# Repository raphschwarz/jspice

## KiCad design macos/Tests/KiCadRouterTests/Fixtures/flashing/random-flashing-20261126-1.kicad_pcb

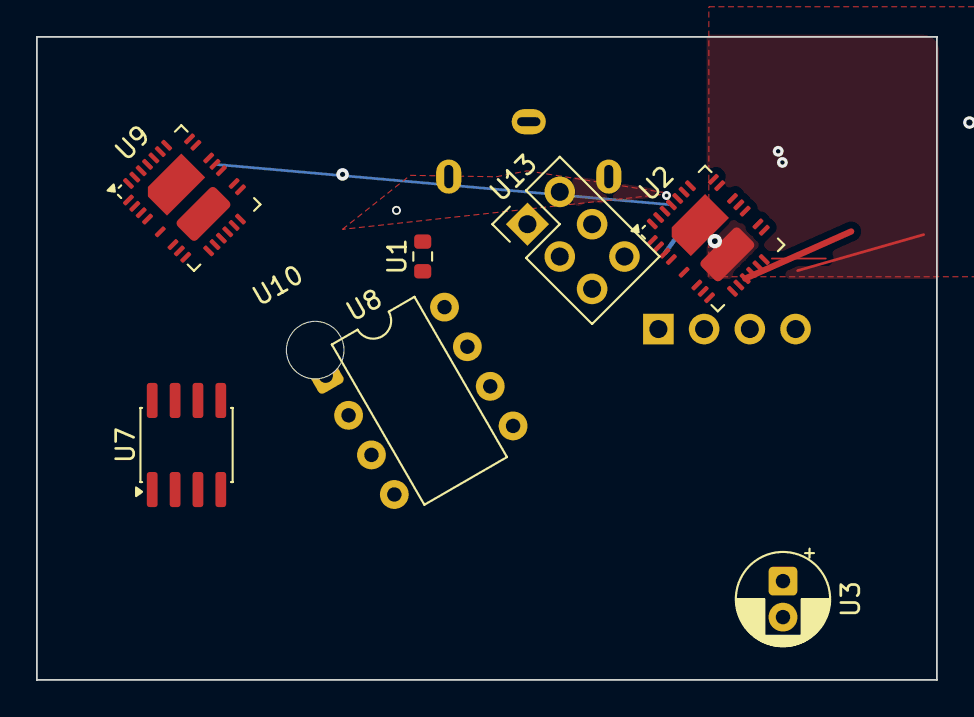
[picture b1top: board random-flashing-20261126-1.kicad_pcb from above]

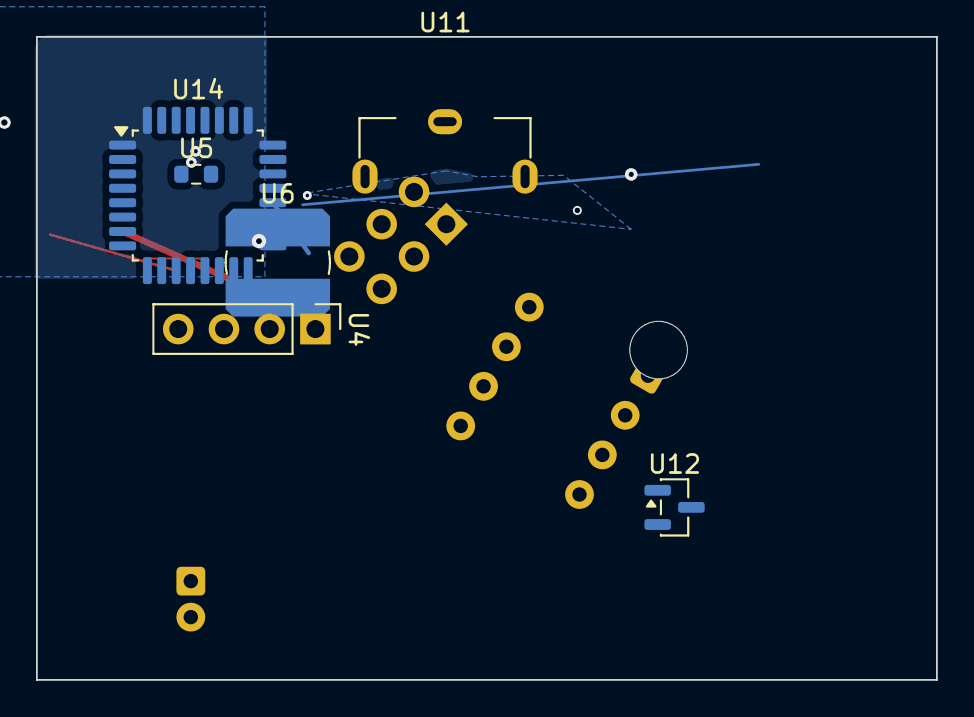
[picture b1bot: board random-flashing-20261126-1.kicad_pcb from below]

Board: 2 copper layers, 50.0 x 35.7 mm, 14 parts (6 on the bottom side), 4 nets.

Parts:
U1, U5: R_0603_1608Metric
U2, U9: Analog_QFN-28-36-2EP_5x6mm_P0.5mm
U3: CP_Radial_D5.0mm_P2.00mm
U4: PinHeader_1x04_P2.54mm_Vertical
U6: L_Bourns_SDR0604
U7: SOIC-8_3.9x4.9mm_P1.27mm
U8: DIP-8_W7.62mm
U10: MountingHole_3.2mm_M3
U11: BatteryHolder_Keystone_590
U12: SOT-23
U13: PinHeader_2x03_P2.54mm_Vertical
U14: LQFP-32_7x7mm_P0.8mm

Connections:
D12: U1.1, U2.1, U2.9, U2.10, U2.14, U2.30, U2.34, U6.2, U7.1, U7.5, U7.7, U8.8, U9.1, U9.31, U11.1, U13.2, U14.3, U14.6, U14.10, U14.12, U14.18, U14.28, U14.29
N1: U2.2, U2.3, U2.17, U2.20, U2.23, U2.31, U2.33, U2.35, U2.37, U4.4, U5.1, U7.2, U8.3, U8.5, U8.7, U9.4, U9.12, U9.15, U9.23, U9.30, U9.34, U9.35, U11.1, U12.1, U13.1, U14.2, U14.5, U14.16
N2: U1.2, U2.6, U2.12, U2.13, U2.38, U3.2, U4.3, U7.6, U8.1, U9.3, U9.6, U9.9, U9.25, U9.38, U14.1, U14.11, U14.19, U14.22, U14.24, U14.25, U14.27, U14.32
VCC: U2.8, U2.15, U2.16, U2.24, U2.36, U3.1, U4.1, U6.1, U8.2, U8.4, U8.6, U9.8, U9.16, U9.21, U9.28, U9.33, U9.36, U12.3, U13.4, U13.6, U14.4, U14.7, U14.13, U14.26, U14.30

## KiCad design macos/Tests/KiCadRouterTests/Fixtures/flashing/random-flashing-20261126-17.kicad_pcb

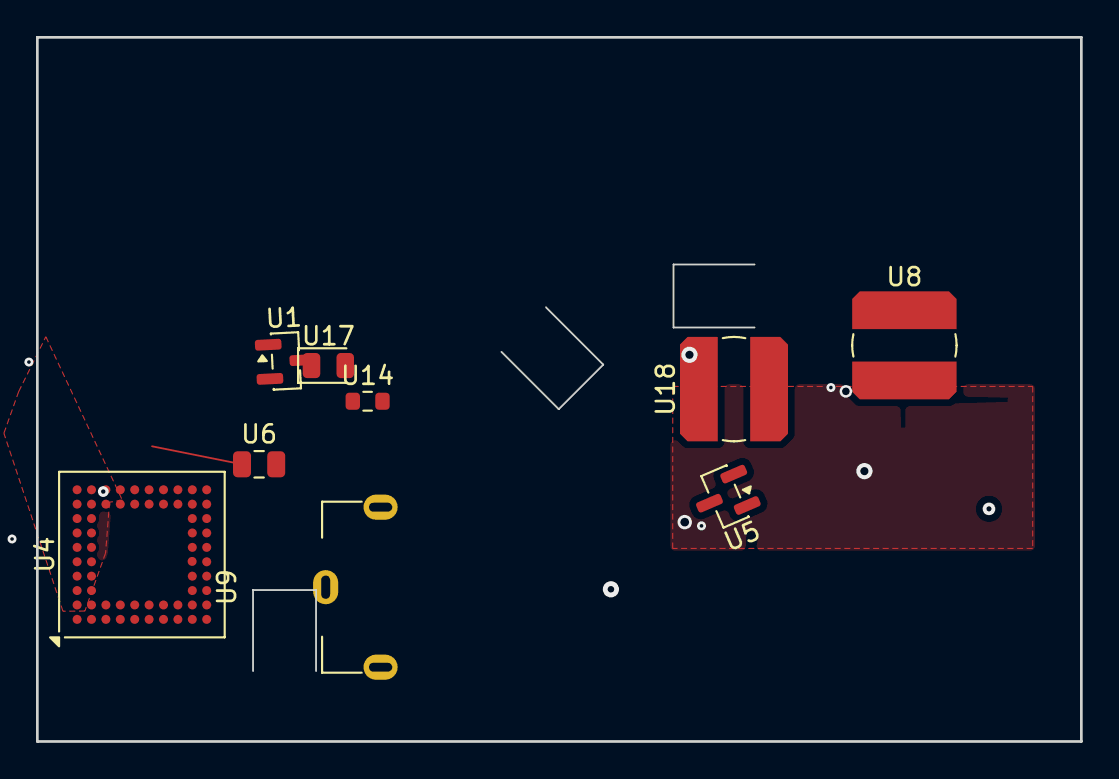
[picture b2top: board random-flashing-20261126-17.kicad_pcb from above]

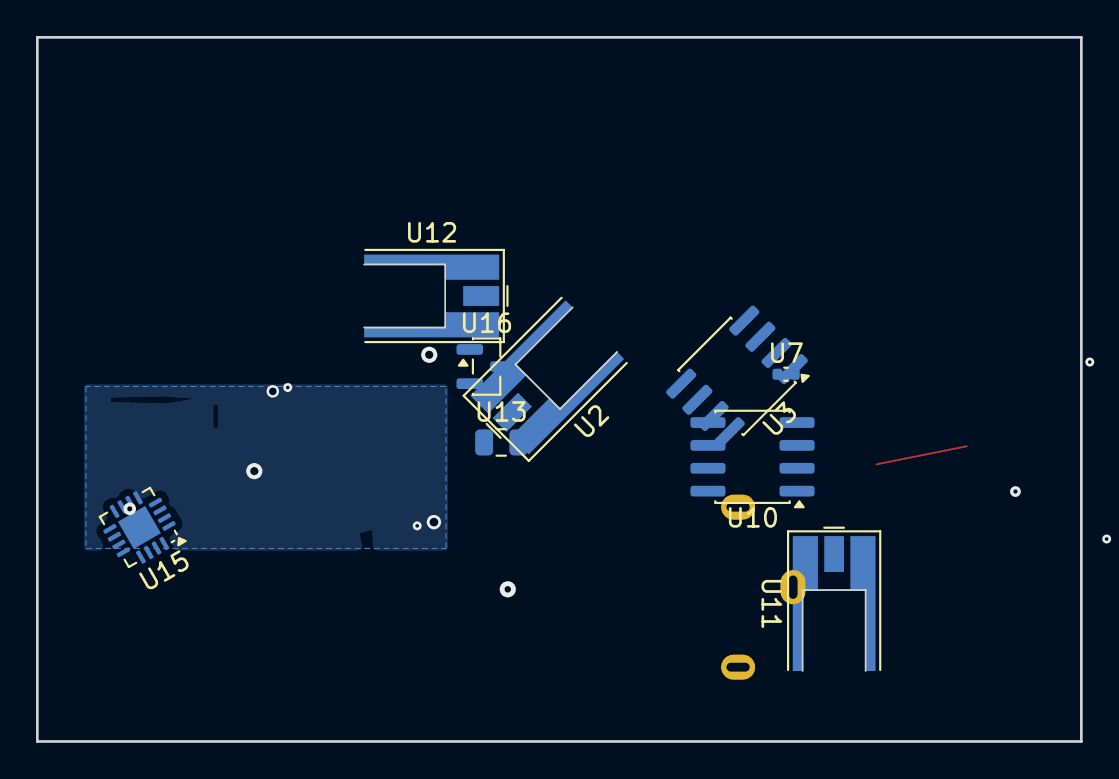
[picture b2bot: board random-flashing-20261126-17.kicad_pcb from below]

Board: 4 copper layers, 58.0 x 39.1 mm, 18 parts (9 on the bottom side), 8 nets.

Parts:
U1, U5, U16: SOT-23
U2, U11, U12: MMCX_Molex_73415-0961_Horizontal_0.8mm-PCB
U3, U10: SOIC-8_3.9x4.9mm_P1.27mm
U4: BGA-64_9.0x9.0mm_Layout10x10_P0.8mm
U6, U13: C_0805_2012Metric
U7: C_0402_1005Metric
U8, U18: L_Bourns_SDR0604
U9: BatteryHolder_Keystone_590
U14: R_0603_1608Metric
U15: QFN-16-1EP_3x3mm_P0.5mm_EP1.75x1.75mm
U17: LED_0805_2012Metric

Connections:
/sub/clk: U1.1, U5.3, U10.5, U10.7, U15.2, U15.12, U15.14
D7: U1.2, U4.B2, U4.B7, U4.G10, U4.H9, U4.J2, U4.J3, U4.K6, U10.1, U10.4, U11.2, U18.1, U18.2
GND: U2.2, U3.8, U4.A10, U4.B8, U4.C10, U4.F9, U4.G2, U4.G9, U4.K2, U8.2, U12.2, U15.5, U15.8, U15.15
N1: U3.2, U4.A7, U4.D1, U4.D9, U4.D10, U4.E1, U4.F2, U4.H10, U4.J4, U4.K8, U10.2, U10.6, U11.1, U13.2, U14.2, U15.7, U15.11, U15.17
N2: U1.3, U3.4, U3.7, U11.2, U15.1
N3: U2.1, U4.B5, U4.F1, U4.H1, U4.J5, U4.K1, U4.K10, U5.1, U6.2, U9.1, U10.3, U12.1, U16.1
PWR1: U3.5, U4.A3, U4.A4, U4.A6, U4.C9, U4.D2, U4.E2, U4.J1, U4.J6, U4.J8, U4.J9, U4.K5, U9.1, U15.3
VCC: U2.2, U4.B3, U4.B4, U4.B10, U4.C2, U4.E9, U4.H2, U4.K9, U14.1, U15.13, U16.2, U17.2

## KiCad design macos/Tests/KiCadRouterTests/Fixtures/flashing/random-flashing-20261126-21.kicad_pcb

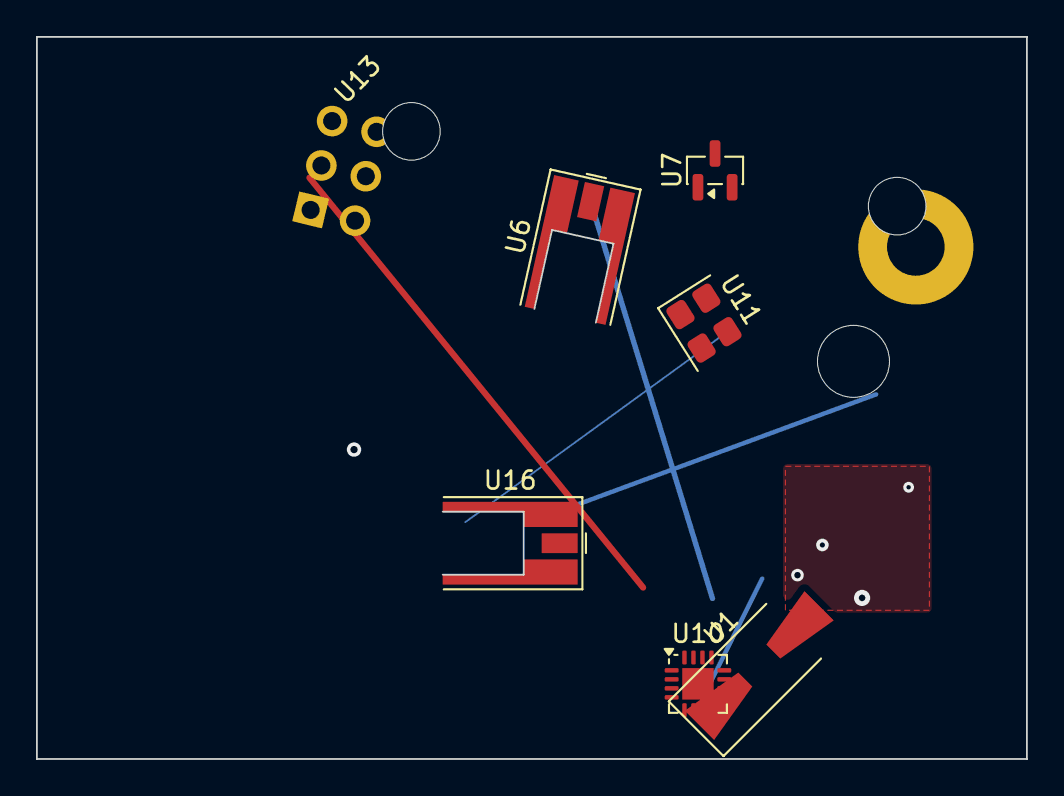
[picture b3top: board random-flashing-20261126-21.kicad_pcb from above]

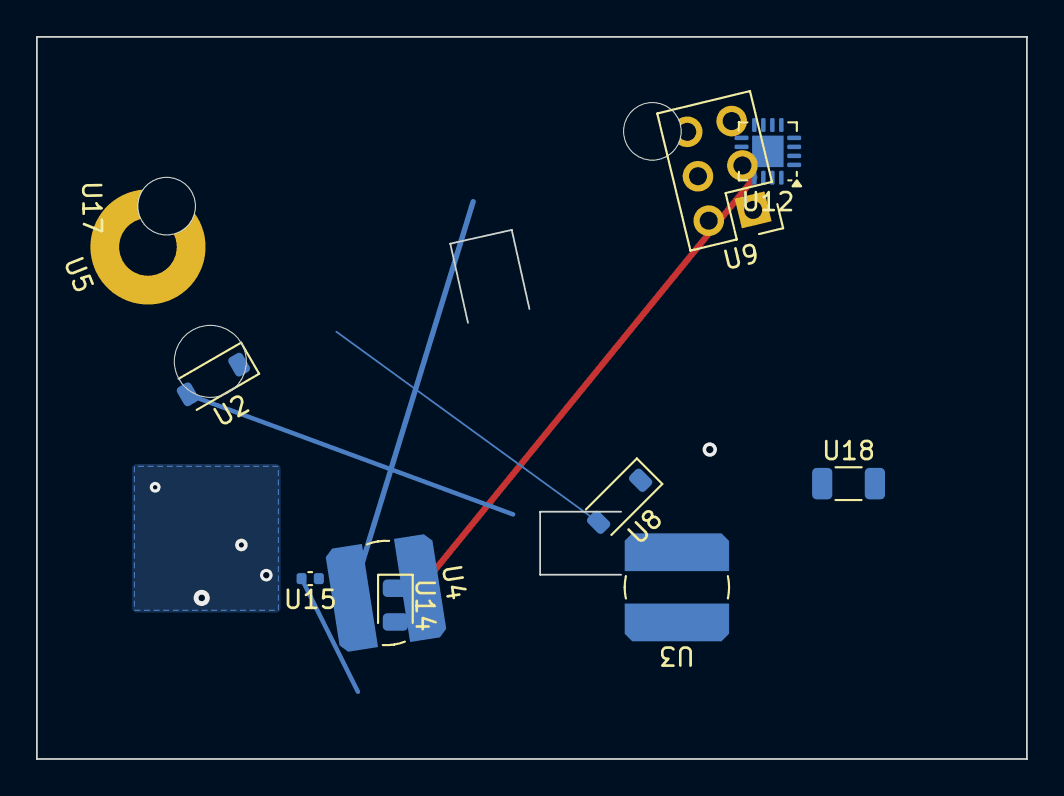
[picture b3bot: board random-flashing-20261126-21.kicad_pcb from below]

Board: 4 copper layers, 55.0 x 40.1 mm, 18 parts (11 on the bottom side), 5 nets.

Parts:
U1: D_SMA-SMB_Universal_Handsoldering
U2, U8: D_SOD-123
U3, U4: L_Bourns_SDR0604
U5: MountingHole_3.2mm_M3_Pad
U6, U16: MMCX_Molex_73415-0961_Horizontal_0.8mm-PCB
U7: SOT-23
U9: PinHeader_2x03_P2.54mm_Vertical
U10, U12: QFN-16-1EP_3x3mm_P0.5mm_EP1.75x1.75mm
U11: Crystal_SMD_3225-4Pin_3.2x2.5mm
U13, U17: MountingHole_3.2mm_M3
U14: LED_0805_2012Metric
U15: C_0402_1005Metric
U18: R_1206_3216Metric

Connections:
/net3: U3.1, U9.1, U10.4, U10.6, U11.2, U12.3, U12.13, U12.16
D7: U1.2, U2.1, U4.2, U8.2, U9.3, U10.5, U10.7, U10.13
D12: U1.1, U4.1, U6.1, U6.2, U7.2, U9.2, U9.5, U10.1, U10.8, U12.4, U12.6, U12.8, U15.1, U15.2
PWR_5V: U2.2, U9.6, U10.3, U10.16, U11.1, U11.3, U12.7, U12.9, U12.14, U12.17, U16.2, U18.1
VCC: U6.2, U7.3, U10.10, U10.11, U10.12, U10.15, U10.17, U11.4, U12.2, U12.10, U12.11, U14.1, U16.1, U16.2

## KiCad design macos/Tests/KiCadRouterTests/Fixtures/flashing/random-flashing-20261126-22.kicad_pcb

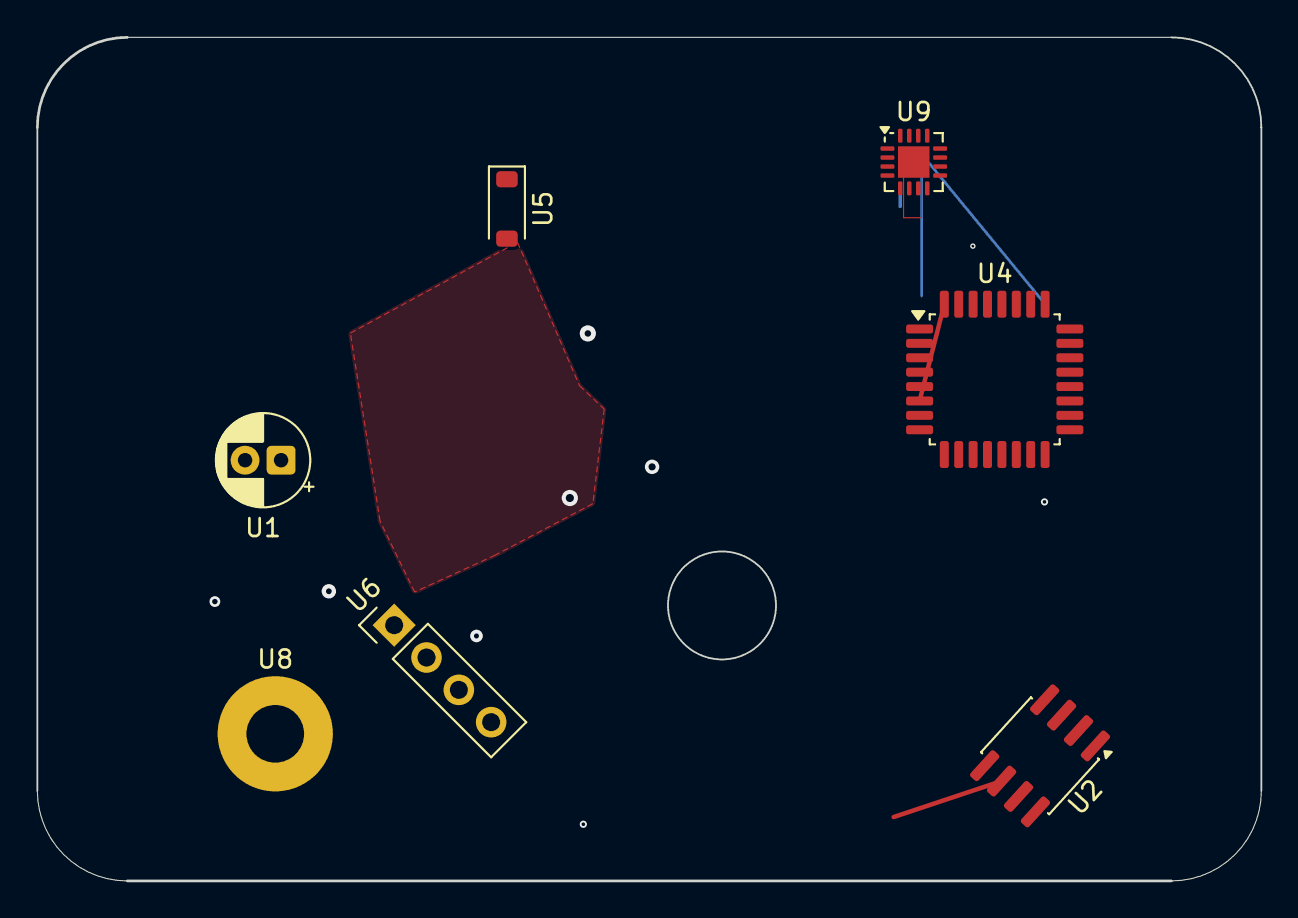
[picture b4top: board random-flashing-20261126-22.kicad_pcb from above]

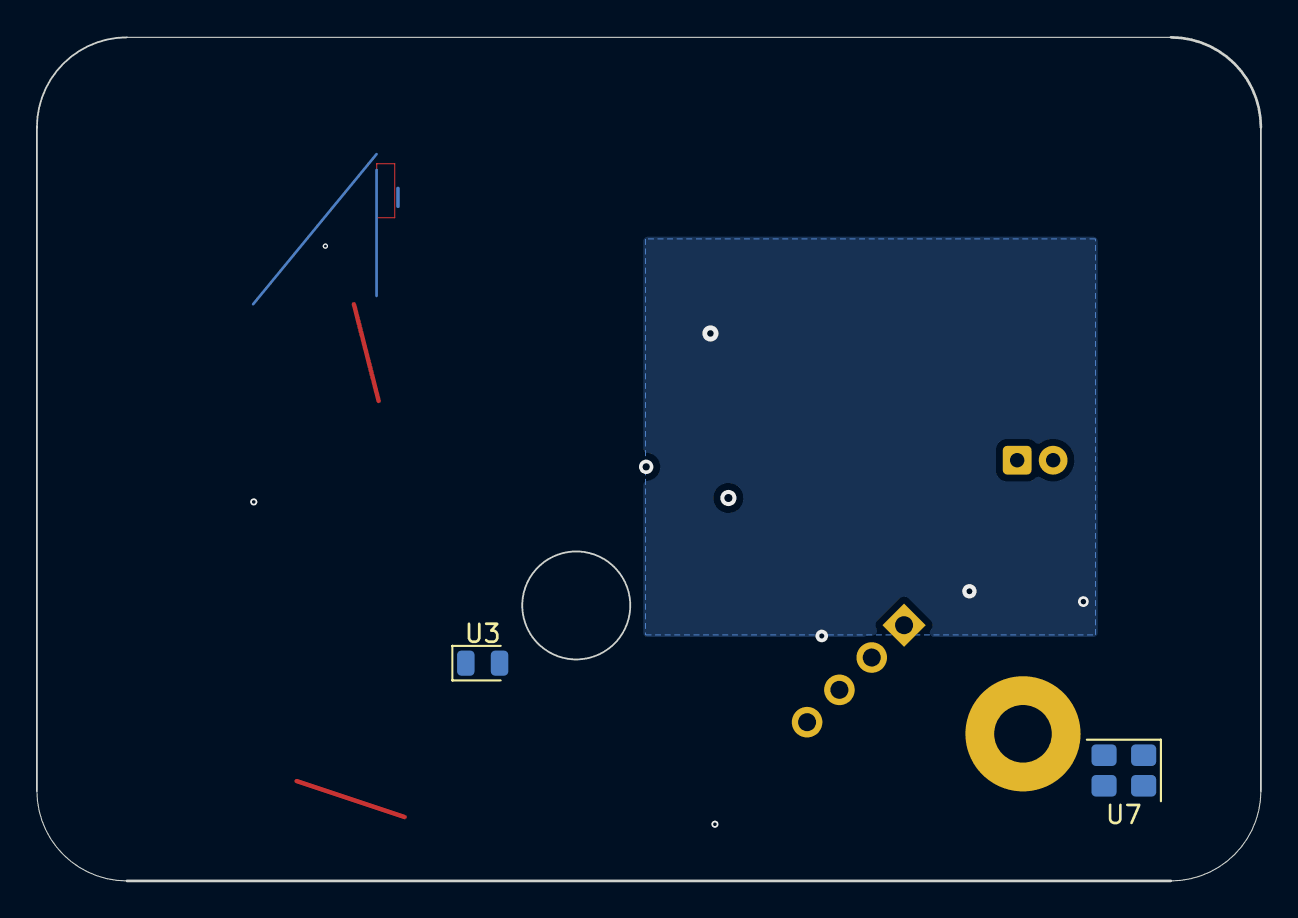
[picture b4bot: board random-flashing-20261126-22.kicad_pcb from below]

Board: 4 copper layers, 68.0 x 46.9 mm, 9 parts (2 on the bottom side), 5 nets.

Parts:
U1: CP_Radial_D5.0mm_P2.00mm
U2: SOIC-8_3.9x4.9mm_P1.27mm
U3: LED_0805_2012Metric
U4: LQFP-32_7x7mm_P0.8mm
U5: D_SOD-123
U6: PinHeader_1x04_P2.54mm_Vertical
U7: Crystal_SMD_3225-4Pin_3.2x2.5mm
U8: MountingHole_3.2mm_M3_Pad
U9: QFN-16-1EP_3x3mm_P0.5mm_EP1.75x1.75mm

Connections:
D7: U1.1, U2.1, U4.2, U4.17, U4.23, U4.29, U6.1, U7.1, U9.6, U9.14, U9.15, U9.17
D12: U2.4, U4.7, U4.20, U4.30, U7.4
GND: U2.6, U2.8, U3.2, U4.6, U4.14, U4.19, U4.22, U4.28, U4.31, U6.3, U9.3, U9.13
N2: U2.7, U3.1, U4.12, U4.15, U4.16, U4.18, U4.27, U4.32, U7.2, U7.3, U9.1, U9.5, U9.7, U9.10, U9.16
PWR_5V: U2.2, U2.3, U4.4, U4.5, U4.8, U4.26, U6.2, U6.4, U9.8
